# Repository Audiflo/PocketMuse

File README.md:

# PocketMage PDA
PocketMage is available on Crowd Supply! Check it out [here](https://pocketmage.org/back)!

@Ashtf 2025

## [Project Summary]

  This project is a PDA powered by an ESP32-S3 running a custom OS written in C++ using PlatformIO. This project utilizes an E-Ink and OLED screen in tandem to mitigate the refresh rate restrictions of an E-Ink panel while retaining the aesthetics and benefits of using E-Ink. This project is a work in progress and currently amounts to a simple GUI for navigating between apps, a text (.txt) file editor, and a basic file manager. More applications are planned for the future and a list of TO-DOs can be found below.

  At this point, the plan for this project is to get the software and hardware to maturity and once a finished product is achieved, a few things will happen. First, the project files (Code, KiCad schematics, 3D files) will be open-sourced and free for anyone to access. Next, I will likely begin selling kits that allow people to purchase all the parts required to build a device for themselves if they don't want to source the parts themselves. Finally, the community will be encouraged to help develop the software for the device and hopefully push it even further than I could myself.

  I will try my best to keep this GitHub up to date with the development of the device.

## [Getting Started]

Start with the docs site:

- [PocketMage Docs](https://tailsmandesign.github.io/PocketMage_PDA/docs/)
- [Build Environments](https://tailsmandesign.github.io/PocketMage_PDA/docs/development/build-environments)
- [Command Manual](https://tailsmandesign.github.io/PocketMage_PDA/docs/command-manual)
- [FAQ](https://tailsmandesign.github.io/PocketMage_PDA/docs/faq)
- [Scripting](https://tailsmandesign.github.io/PocketMage_PDA/docs/scripting)
- [App API Reference](https://tailsmandesign.github.io/PocketMage_PDA/docs/reference/app-api)

To build or extend apps, start with [APP_TEMPLATE.cpp](./Code/PocketMageOS/src/APP_TEMPLATE.cpp) and the [App API Reference](https://tailsmandesign.github.io/PocketMage_PDA/docs/reference/app-api).
The app walkthrough video is still useful for a first pass:
[Developing For the PocketMage](https://www.youtube.com/watch?v=3Ytc-3-BbMM)

## [Hardware]

- ESP32-S3 WROOM1 with 16 MB flash and 8 MB RAM. WiFi and Bluetooth supported.
- 3.1" 320x240px 1-bit SPI E-Ink panel (GDEQ031T10) with integrated driver
- 256x32px 1-bit SPI OLED (SSD1326, ER-OLED018-1W) with integrated driver
- MicroSD card slot with support for up to 2 TB
- TCA8418 I2C keyboard matrix IC
- Piezo buzzer (simple tones)
- Power button
- 1200 mAh pouch-style LiPo battery with JST PH (2 mm) connector
- USB Type-C connector
- PCF8563T I2C RTC module
- Expansion port with the following breakouts:
  - +3.3V
  - GND
  - I2C SDA
  - I2C SCL
  - SPI MOSI
  - SPI SCK
  - SPI MISO
  - GPIO A
  - GPIO B
  - GPIO C
  - GPIO D / UART TX (changeable with a solder jumper, default TX)
  - GPIO E / UART RX (changeable with a solder jumper, default RX)

## [Software]

- Text editor app (TXT)
- FileWiz file-management app
- Calendar app
- USB file transfer app
- COMM mesh chat app
- Settings app
- Tasks app
- Journal app
- Dictionary app (Lexicon)
- App loader for OTA apps
- Terminal app (Wrench scripting)
- SSH
- Commands supported through the home menu:
  - `roll dN` (dice roll, N = number of sides)
  - set time and date
  - directly open files in TXT or FileWiz by typing the name
  - and more

## [Planned Features]

- Timers and alarms
- E-book reader
- WiFi notes/calendar sync (Google Docs/Calendar)
- LoRa/Meshtastic add-on module
- Battery expansion add-on module
- Custom abbreviations
- Bluetooth keyboard support

## License

All files are distributed under the Apache-2.0 license:

PocketMage PDA - A clamshell note-taking and productivity device using E-Ink and OLED.

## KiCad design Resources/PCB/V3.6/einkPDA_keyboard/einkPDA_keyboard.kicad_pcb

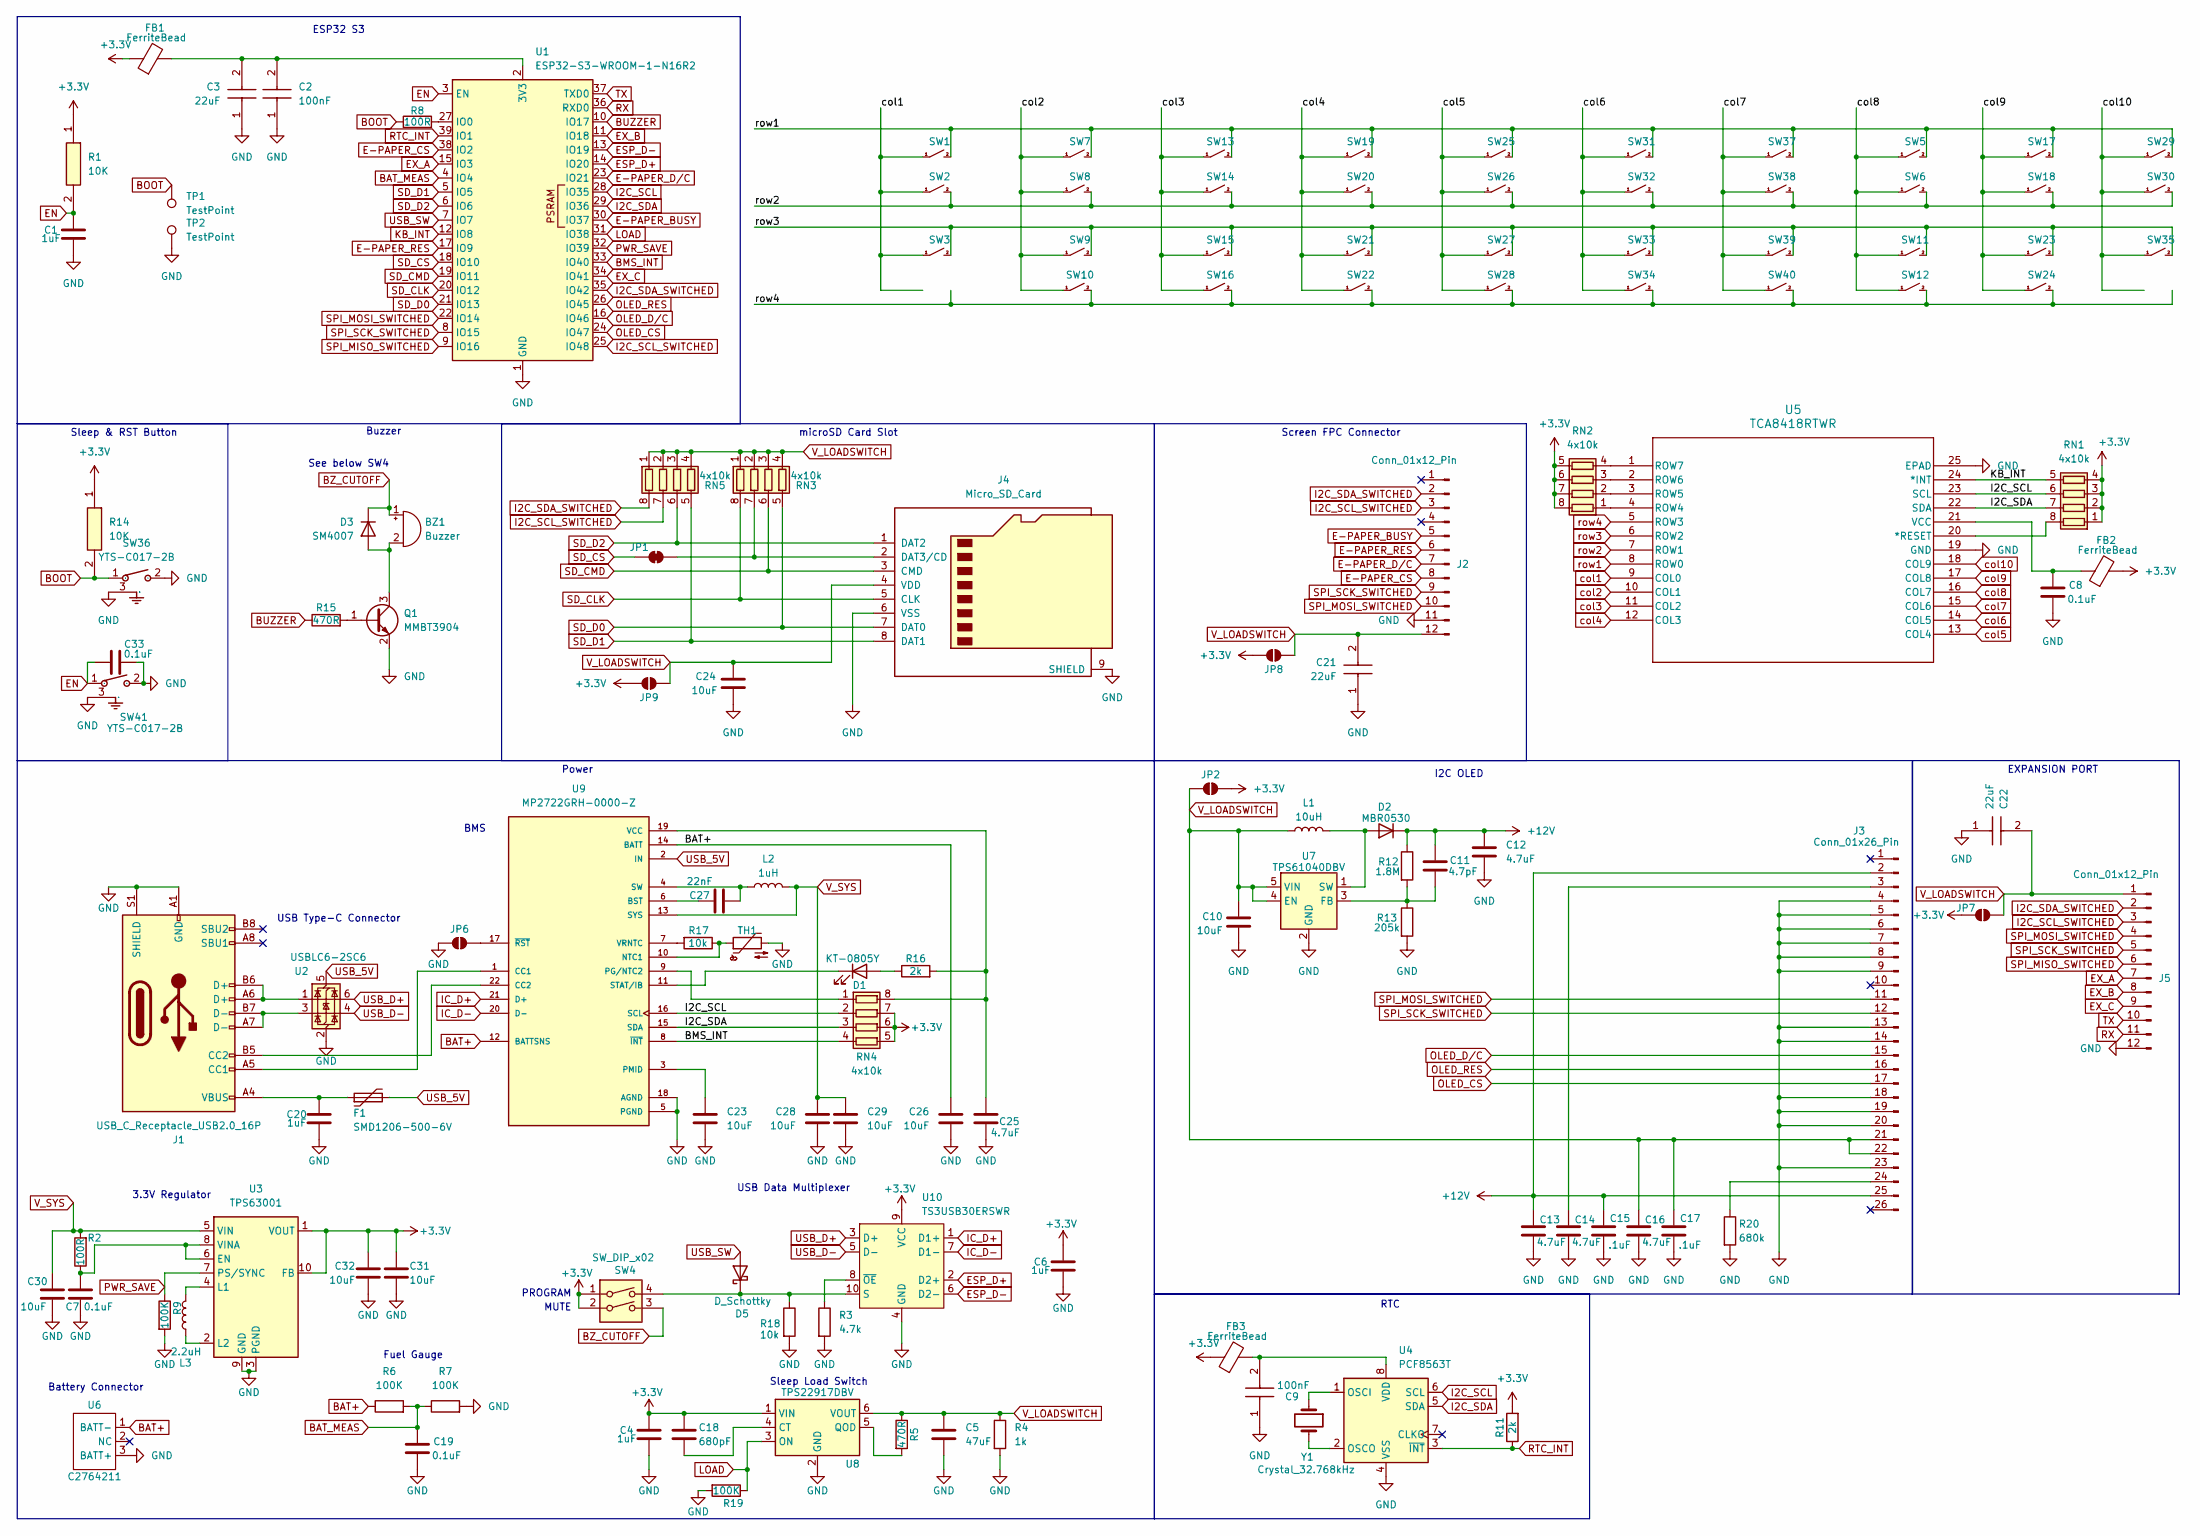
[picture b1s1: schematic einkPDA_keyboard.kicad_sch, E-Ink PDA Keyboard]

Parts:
BZ1: Buzzer; BUZ-SMD_3P_L5.0-W5.0-P3.50-TL; LCSC Part # C781883
C1, C4, C6, C20: 1uF; C_0603_1608Metric; LCSC Part # C15849
C2, C9: 100nF; C_0805_2012Metric; Mouser Part Number 603-CC805KRX7R9BB104
C3, C21, C22: 22uF; C_0805_2012Metric; Mouser Part Number 187-CL21A226MAQNNNE
C5: 47uF; C_0805_2012Metric; LCSC Part # C124129
C7, C8, C19, C33: 0.1uF; C_0402_1005Metric; LCSC Part # C1525
C10, C23, C26, C28, C29, C30, C31, C32: 10uF; C_0805_2012Metric; LCSC PART # C15850
C11: 4.7pF; C_0603_1608Metric; LCSC PART # C1669
C12, C13, C14, C16: 4.7uF; C_1206_3216Metric; LCSC PART # C29823
C15, C17: .1uF; C_0805_2012Metric; LCSC PART # C28233
C18: 680pF; C_0805_2012Metric; LCSC Part # C1754
C24: 10uF; C_0805_2012Metric; LCSC Part # C15850
C25: 4.7uF; C_0805_2012Metric; LCSC Part # C1779
C27: 22nF; C_0603_1608Metric; LCSC Part # C21122
D1: KT-0805Y; LED_0805_2012Metric; LCSC Part # C2296
D2: MBR0530; D_SOD-123; LCSC PART # C77336
D3: SM4007; D_SOD-123F; LCSC Part # C64898
D5: D_Schottky; D_SOD-323; LCSC Part # C191023
F1: SMD1206-500-6V; Fuse_1206_3216Metric; LCSC Part # C2760308
FB1, FB2, FB3: FerriteBead; L_0603_1608Metric; LCSC Part # C85831
J1: USB_C_Receptacle_USB2.0_16P; USB-TYPE-C-SMD_TYPE-C-16P-QTWT; LCSC Part # C5187472
J2, J5: Conn_01x12_Pin; AFC01-S12FCA-00; LCSC Part # C262661
J3: Conn_01x26_Pin; FPC-SMD_AFC24-S26FIA [DUAL-SIDE]; LCSC PART # C262684
J4: Micro_SD_Card; TF-SMD_503398-1892; LCSC Part # C428492
JP1: SolderJumper_2_Bridged; SolderJumper-2_P1.3mm_Bridged_RoundedPad1.0x1.5mm
JP2, JP6, JP7, JP8, JP9: SolderJumper_2_Open; SolderJumper-2_P1.3mm_Open_RoundedPad1.0x1.5mm
L1: 10uH; L_Chilisin_BMRx00060630; LCSC PART # C5189958
L2: 1uH; L_Ferrocore_DLG-0504; LCSC Part # C2929426
L3: 2.2uH; L_Wurth_WE-LQSH-3012; LCSC Part # C167747
Q1: MMBT3904; SOT-23; LCSC Part # C20526
R1, R14: 10K; R_0805_2012Metric; Mouser Part Number 303-0805W8F1002T5E
R2, R8: 100R; R_0603_1608Metric; LCSC Part # C22775
R3: 4.7k; R_0603_1608Metric; LCSC Part # C23162
R4: 1k; R_0603_1608Metric; LCSC Part # C21190
R5, R15: 470R; R_0805_2012Metric; LCSC Part # C17710
R6, R7, R9, R19: 100K; R_0603_1608Metric; LCSC Part # C25803
R11, R16: 2k; R_0805_2012Metric; LCSC Part # C17604
R12: 1.8M; R_0805_2012Metric; LCSC PART # C17399
R13: 205k; R_0805_2012Metric; LCSC PART # C218417
R17: 10k; R_0805_2012Metric; LCSC Part # C17414
R18: 10k; R_0603_1608Metric; LCSC Part # C25804
R20: 680k; R_0805_2012Metric; LCSC PART # C17797
RN1, RN2, RN3, RN4, RN5: 4x10k; R_Array_Concave_4x0603; LCSC Part # C29718
SW1, SW2, SW3, SW5, SW6, SW7, SW8, SW9, SW10, SW11, SW12, SW13, SW14, SW15, SW16, SW17, SW18, SW19, SW20, SW21, SW22, SW23, SW24, SW25, SW26, SW27, SW28, SW29, SW30, SW31, SW32, SW33, SW34, SW35, SW37, SW38, SW39, SW40: contact_pad_SINGLE
SW4: SW_DIP_x02; 2X_DIP_DHN-02-V-TR; LCSC Part # C224995
SW36, SW41: YTS-C017-2B; KEY-TH_3P-L4.5-W4.5-P3.0-EH; Manufacturer Part YTS-C017-2B; LCSC Part # C2910872
TH1: NTC; R_0603_1608Metric; LCSC Part # C76589
TP1, TP2: TestPoint; TestPoint_Pad_1.0x1.0mm
U1: ESP32-S3-WROOM-1-N16R2; ESP32-S3-WROOM-1; LCSC Part # C2913205
U2: USBLC6-2SC6; SOT-23-6; LCSC Part # C7519
U3: TPS63001; Texas_DRC0010J_ThermalVias; LCSC Part # C28060
U4: PCF8563T; SOIC-8_3.9x4.9mm_P1.27mm; LCSC Part # C7440
U5: TCA8418RTWR; RTW24_2P45X2P45; LCSC Part # C138713
U6: C2764211; CONN-SMD_532610271; LCSC Part # C2764211
U7: TPS61040DBV; SOT-23-5; LCSC PART # C7722
U8: TPS22917DBV; SOT-23-6; LCSC Part # C2680344
U9: MP2722GRH-0000-Z; IC_MP2722GRH-0000-Z; PARTREV 1.0; LCSC Part # C20099551
U10: TS3USB30ERSWR; UQFN-10_1.4x1.8mm_P0.4mm; LCSC Part # C73880
Y1: Crystal_32.768kHz; Crystal_SMD_3215-2Pin_3.2x1.5mm; LCSC Part # C5213671

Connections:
+3.3V: C4.2, C6.2, C18.1, C31.2, C32.2, FB1.1, FB2.2, FB3.1, JP2.2 (B), JP7.2 (B), JP8.2 (B), JP9.2 (B), R1.1, R11.2, R14.1, RN1.1 (R1.1), RN1.2 (R2.1), RN1.3 (R3.1), RN1.4 (R4.1), RN2.5 (R4.2), RN2.6 (R3.2), RN2.7 (R2.2), RN2.8 (R1.2), RN4.5 (R4.2), RN4.6 (R3.2), RN4.7 (R2.2), SW4.1, SW4.2, U3.1 (VOUT), U3.10 (FB), U8.1 (VIN), U10.9 (VCC)
+12V: C11.2, C12.1, C13.1, C15.1, D2.1 (K), J3.2, J3.25, R12.1
BAT+: C26.2, R6.1, U6.1 (BATT-), U9.12 (BATTSNS), U9.14 (BATT)
BAT_MEAS: C19.1, R6.2, R7.1, U1.4 (IO4)
BMS_INT: RN4.4 (R4.1), U1.33 (IO40), U9.8 (~INT)
BOOT: R8.1, R14.2, SW36.1, TP1.1
BUZZER: R15.1, U1.10 (IO17)
BZ_CUTOFF: BZ1.1 (+), D3.1 (K), SW4.3
E-PAPER_BUSY: J2.5, U1.30 (IO37)
E-PAPER_CS: J2.8, U1.38 (IO2)
E-PAPER_D/C: J2.7, U1.23 (IO21)
E-PAPER_RES: J2.6, U1.17 (IO9)
EN: C1.2, C33.1, R1.2, SW41.1, U1.3 (EN)
ESP_D+: U1.14 (IO20), U10.2 (D2+)
ESP_D-: U1.13 (IO19), U10.6 (D2-)
EX_A: J5.7, U1.15 (IO3)
EX_B: J5.8, U1.11 (IO18)
EX_C: J5.9, U1.34 (IO41)
GND: C1.1, C2.1, C3.1, C4.1, C5.2, C6.1, C7.2, C8.2, C9.1, C10.1, C12.2, C13.2, C14.2, C15.2, C16.2, C17.2, C19.2, C20.1, C21.1, C22.1, C23.1, C24.2, C25.2, C26.1, C28.1, C29.1, C30.1, C31.1, C32.1, C33.2, J1.A1 (GND), J1.A12 (GND), J1.B1 (GND), J1.B12 (GND), J1.S1 (SHIELD), J2.11, J3.4, J3.5, J3.6, J3.7, J3.8, J3.9, J3.13, J3.14, J3.18, J3.19, J3.20, J3.23, J4.6 (VSS), J4.9 (SHIELD), J5.12, JP6.1 (A), Q1.2 (E), R3.2, R4.2, R7.2, R9.2, R13.2, R18.2, R19.2, R20.2, SW36.2, SW36.3 (GND), SW41.2, SW41.3 (GND), TH1.2, TP2.1, U1.1 (GND), U1.40 (GND), U1.41 (GND), U2.2 (GND), U3.3 (PGND), U3.9 (GND), U3.11 (PGND), U4.4 (VSS), U5.19 (GND), U5.25 (EPAD), U6.3 (BATT+), U7.2 (GND), U8.2 (GND), U9.5 (PGND), U9.18 (AGND), U10.4 (GND)
I2C_SCL: RN1.6 (R3.2), RN4.2 (R2.1), U1.28 (IO35), U4.6 (SCL), U5.23 (SCL), U9.16 (SCL)
I2C_SCL_SWITCHED: J2.3, J5.3, RN5.7 (R2.2), U1.25 (IO48)
I2C_SDA: RN1.7 (R2.2), RN4.3 (R3.1), U1.29 (IO36), U4.5 (SDA), U5.22 (SDA), U9.15 (SDA)
I2C_SDA_SWITCHED: J2.2, J5.2, RN5.8 (R1.2), U1.35 (IO42)
IC_D+: U9.21 (D+), U10.1 (D1+)
IC_D-: U9.20 (D-), U10.7 (D1-)
KB_INT: RN1.5 (R4.2), U1.12 (IO8), U5.24 (*INT)
LOAD: R19.1, U1.31 (IO38), U8.3 (ON)
unnamed: BZ1.2 (-), D3.2 (A), Q1.3 (C)
unnamed: C20.2, F1.1, J1.A4 (VBUS), J1.A9 (VBUS), J1.B4 (VBUS), J1.B9 (VBUS)
unnamed: D1.2 (A), R16.1
unnamed: D1.1 (K), U9.11 (STAT/IB)
unnamed: D2.2 (A), L1.2, U7.1 (SW)
unnamed: D5.1 (K), R18.1, SW4.4, U10.10 (S)
unnamed: J1.A5 (CC1), U9.1 (CC1)
unnamed: J1.B5 (CC2), U9.22 (CC2)
unnamed: J1.A6 (D+), J1.B6 (D+), U2.1 (I/O1)
unnamed: J1.A7 (D-), J1.B7 (D-), U2.3 (I/O2)
unnamed: C14.1, J3.3
unnamed: J3.24, R20.1
unnamed: J4.2 (DAT3/CD), JP1.2 (B), RN3.7 (R2.2)
unnamed: JP6.2 (B), U9.17 (~RST)
unnamed: Q1.1 (B), R15.2
unnamed: RN1.8 (R1.2), U5.20 (*RESET)
unnamed: RN2.1 (R1.1), U5.4 (ROW4)
unnamed: RN2.2 (R2.1), U5.3 (ROW5)
unnamed: RN2.3 (R3.1), U5.2 (ROW6)
unnamed: RN2.4 (R4.1), U5.1 (ROW7)
unnamed: RN4.1 (R1.1), U9.9 (PG/NTC2)
unnamed: C25.1, R16.2, RN4.8 (R1.2), U9.19 (VCC)
unnamed: C2.2, C3.2, FB1.2, U1.2 (3V3)
unnamed: R8.2, U1.27 (IO0)
unnamed: C7.1, R2.1, U3.6 (EN), U3.8 (VINA)
unnamed: L3.1, U3.4 (L1)
unnamed: L3.2, U3.2 (L2)
unnamed: U4.1 (OSCI), Y1.1
unnamed: U4.2 (OSCO), Y1.2
unnamed: C9.2, FB3.2, U4.8 (VDD)
unnamed: C8.1, FB2.1, U5.21 (VCC)
unnamed: C11.1, R12.2, R13.1, U7.3 (FB)
unnamed: C18.2, U8.4 (CT)
unnamed: R5.2, U8.5 (QOD)
unnamed: C27.2, U9.6 (BST)
unnamed: R17.1, TH1.1, U9.10 (NTC1)
unnamed: C23.2, U9.3 (PMID)
unnamed: C27.1, L2.1, U9.4 (SW)
unnamed: R17.2, U9.7 (VRNTC)
unnamed: R3.1, U10.8 (~OE)
OLED_CS: J3.17, U1.24 (IO47)
OLED_D/C: J3.15, U1.16 (IO46)
OLED_RES: J3.16, U1.26 (IO45)
PWR_SAVE: R9.1, U1.32 (IO39), U3.7 (PS/SYNC)
RTC_INT: R11.1, U1.39 (IO1), U4.3 (~INT)
RX: J5.11, U1.36 (RXD0)
SD_CLK: J4.5 (CLK), RN3.8 (R1.2), U1.20 (IO12)
SD_CMD: J4.3 (CMD), RN3.6 (R3.2), U1.19 (IO11)
SD_CS: JP1.1 (A), U1.18 (IO10)
SD_D0: J4.7 (DAT0), RN3.5 (R4.2), U1.21 (IO13)
SD_D1: J4.8 (DAT1), RN5.5 (R4.2), U1.5 (IO5)
SD_D2: J4.1 (DAT2), RN5.6 (R3.2), U1.6 (IO6)
SPI_MISO_SWITCHED: J5.6, U1.9 (IO16)
SPI_MOSI_SWITCHED: J2.10, J3.11, J5.4, U1.22 (IO14)
SPI_SCK_SWITCHED: J2.9, J3.12, J5.5, U1.8 (IO15)
TX: J5.10, U1.37 (TXD0)
USB_5V: F1.2, U2.5 (VBUS), U9.2 (IN)
USB_D+: U2.6 (I/O1), U10.3 (D+)
USB_D-: U2.4 (I/O2), U10.5 (D-)
USB_SW: D5.2 (A), U1.7 (IO7)
V_LOADSWITCH: C5.1, C10.2, C16.1, C17.1, C21.2, C22.2, C24.1, J2.12, J3.21, J3.22, J4.4 (VDD), J5.1, JP2.1 (A), JP7.1 (A), JP8.1 (A), JP9.1 (A), L1.1, R4.1, R5.1, RN3.1 (R1.1), RN3.2 (R2.1), RN3.3 (R3.1), RN3.4 (R4.1), RN5.1 (R1.1), RN5.2 (R2.1), RN5.3 (R3.1), RN5.4 (R4.1), U7.4 (EN), U7.5 (VIN), U8.6 (VOUT)
V_SYS: C28.2, C29.2, C30.2, L2.2, R2.2, U3.5 (VIN), U9.13 (SYS)
col1: SW1.1, SW2.1, SW3.1, U5.9 (COL0)
col2: SW7.1, SW8.1, SW9.1, SW10.1, U5.10 (COL1)
col3: SW13.1, SW14.1, SW15.1, SW16.1, U5.11 (COL2)
col4: SW19.1, SW20.1, SW21.1, SW22.1, U5.12 (COL3)
col5: SW25.1, SW26.1, SW27.1, SW28.1, U5.13 (COL4)
col6: SW31.1, SW32.1, SW33.1, SW34.1, U5.14 (COL5)
col7: SW37.1, SW38.1, SW39.1, SW40.1, U5.15 (COL6)
col8: SW5.1, SW6.1, SW11.1, SW12.1, U5.16 (COL7)
col9: SW17.1, SW18.1, SW23.1, SW24.1, U5.17 (COL8)
col10: SW29.1, SW30.1, SW35.1, U5.18 (COL9)
row1: SW1.2, SW5.2, SW7.2, SW13.2, SW17.2, SW19.2, SW25.2, SW29.2, SW31.2, SW37.2, U5.8 (ROW0)
row2: SW2.2, SW6.2, SW8.2, SW14.2, SW18.2, SW20.2, SW26.2, SW30.2, SW32.2, SW38.2, U5.7 (ROW1)
row3: SW3.2, SW9.2, SW11.2, SW15.2, SW21.2, SW23.2, SW27.2, SW33.2, SW35.2, SW39.2, U5.6 (ROW2)
row4: SW10.2, SW12.2, SW16.2, SW22.2, SW24.2, SW28.2, SW34.2, SW40.2, U5.5 (ROW3)

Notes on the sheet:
ESP32 S3
RTC
Screen FPC Connector
PROGRAM
Buzzer
Battery Connector
See below SW4
Power
microSD Card Slot
Fuel Gauge
Sleep Load Switch
USB Data Multiplexer
USB Type-C Connector
3.3V Regulator
EXPANSION PORT
Sleep & RST Button
MUTE
BMS
I2C OLED

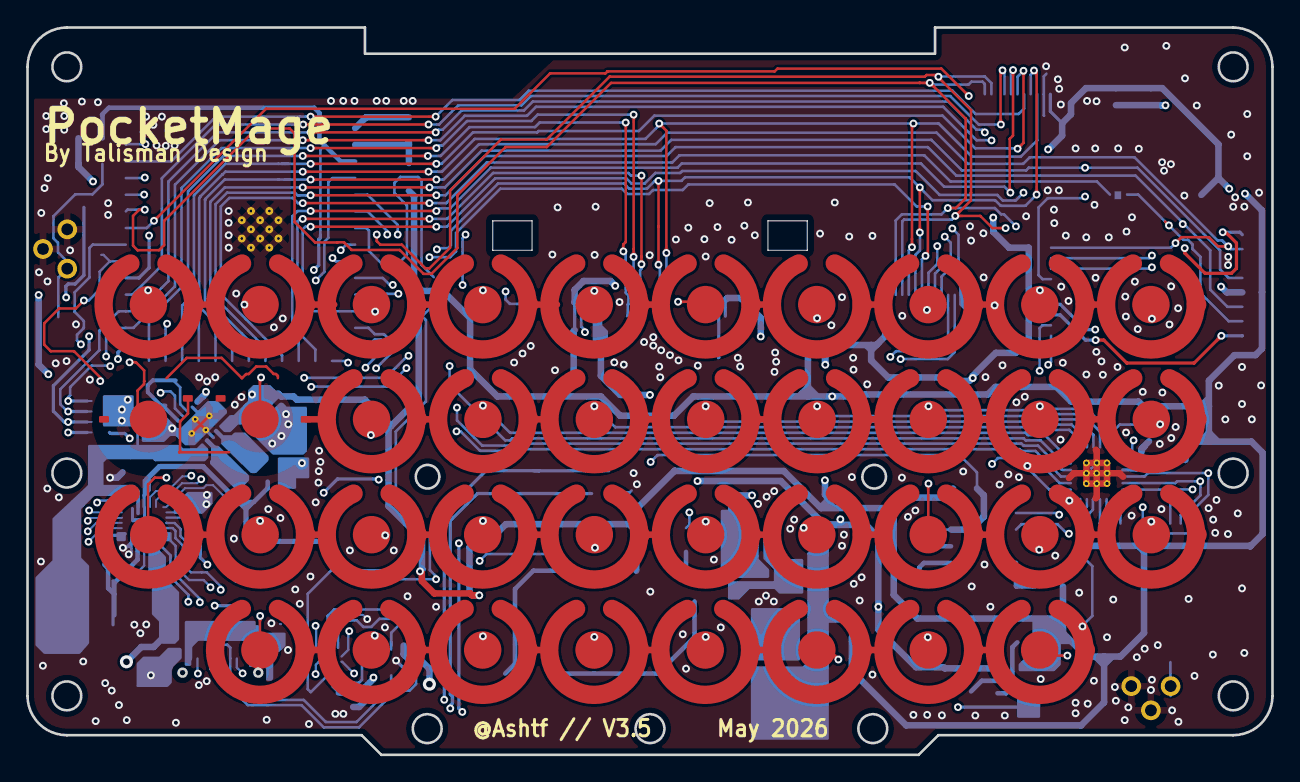
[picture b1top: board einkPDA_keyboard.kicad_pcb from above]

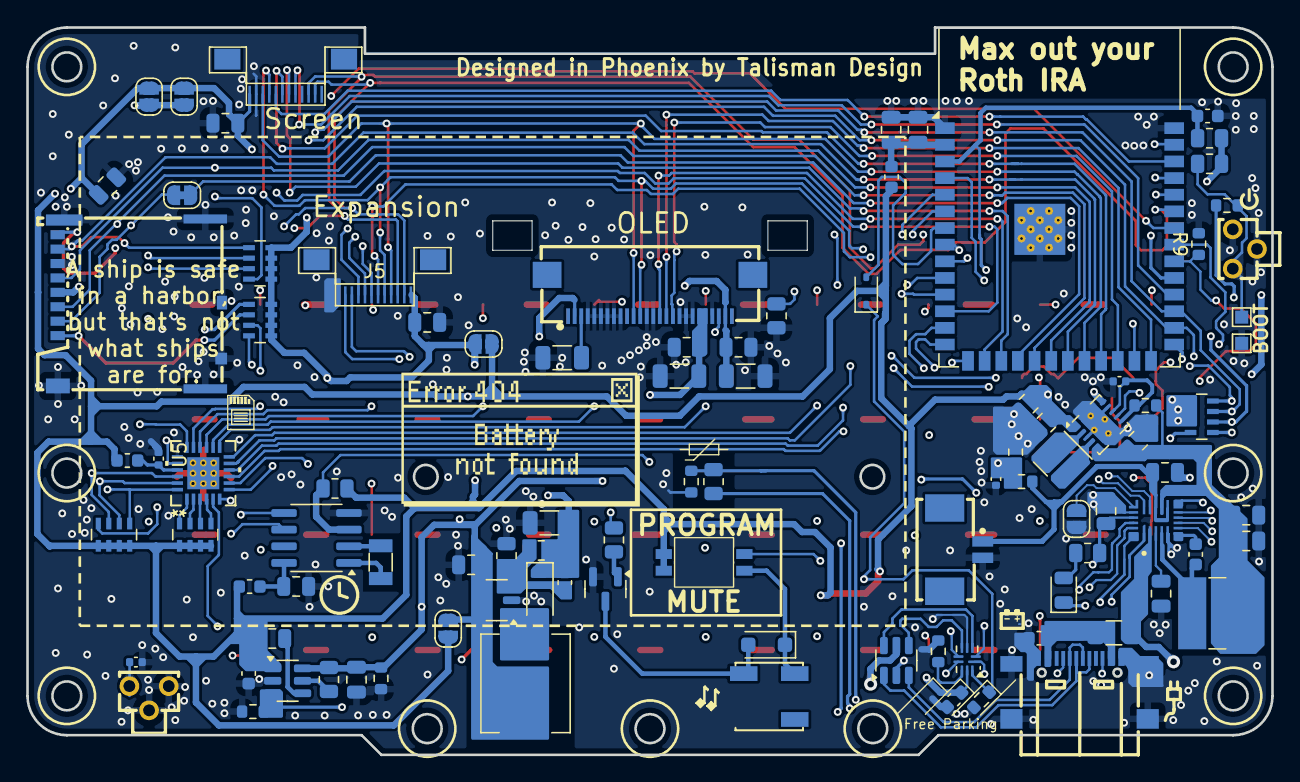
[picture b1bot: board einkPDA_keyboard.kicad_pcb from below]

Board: 4 copper layers, 95.0 x 55.5 mm, 136 parts (98 on the bottom side), 103 nets.

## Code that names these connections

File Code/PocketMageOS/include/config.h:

#ifndef CONFIG_H
#define CONFIG_H

// OTA App
// Is this an OTA APP? // OTA_APP: set -DOTA_APP_FLAG=1 in platformio.ini
#if OTA_APP_FLAG
#define OTA_APP true
#else
#define OTA_APP false
#endif

// CONFIGURATION & SETTINGS
////////////////////////////////////////////////////////////////////////////////////////////////////////////////////////////|
#define KB_COOLDOWN 3                           // Keypress cooldown
#define MAX_FILES 10                            // Number of files to store
#define FORMAT_SPIFFS_IF_FAILED true            // Format the SPIFFS filesystem if mount fails
#define SLEEPMODE "TEXT"                        // TEXT, SPLASH, CLOCK
#define TXT_APP_STYLE 1                         // 0: Old Style (NOT SUPPORTED), 1: New Style
#define SET_CLOCK_ON_UPLOAD false               // Should system clock be set automatically on code upload?
#define TOUCH_TIMEOUT_MS 1200                   // Delay after scrolling to return to typing mode (ms)
#define SYS_METADATA_FILE "/sys/SDMMC_META.txt" // File path to the file system metadata file
#define POWER_SAVE_FREQ 40                      // CPU freq for power save mode
#define IDLE_TIME 20000                         // time to wait for mage idle (ms)

// Full refresh after N refreshes (CHANGE WITH CAUTION)
#define FAST_REFRESH_AFTER 5   // Fast/partial mode: datasheet clean-every-5
#if POCKETMAGE_HW_VERSION == 2
  #define FULL_REFRESH_AFTER 10 // Prod legacy uses N=10                    
#else
  #define FULL_REFRESH_AFTER 5  // Beta needs N=5
#endif
////////////////////////////////////////////////////////////////////////////////////////////////////////////////////////////|

// PIN DEFINITION
#define I2C_SCL       35
#define I2C_SDA       36
#define SWITCHED_I2C_SDA  42
#define SWITCHED_I2C_SCL  48
#define MPR121_ADDR   0x5A
#define MP2722_ADDR   0x3F
#define USB_MUX_PIN   7

#define KB_IRQ        8
#define PWR_BTN       0 
#define BAT_SENS      4
#define CHRG_SENS     39
#define RTC_INT       1 
#define LOAD_SWITCH   38

// SPI
#define SPI_MOSI      14
#define SPI_SCK       15

// OLED
#define OLED_CS       47
#define OLED_DC       46
#define OLED_RST      45

// E Ink
#define EPD_CS        2
#define EPD_DC        21
#define EPD_RST       9
#define EPD_BUSY      37

// SDMMC mode
#define SD_CLK        12
#define SD_CMD        11
#define SD_D0         13
#define SD_D1         5
#define SD_D2         6
#define SD_D3         10

// SDSPI mode
#define SD_CS         10
#define SD_MOSI       11
#define SD_SCK        12
#define SD_MISO       13

#define BZ_PIN        17

// ===================== SYSTEM SETTINGS =====================
// Persistent preferences
extern int TIMEOUT;              // Auto sleep timeout (seconds)
extern bool DEBUG_VERBOSE;       // Extra debug output
extern bool SYSTEM_CLOCK;        // Show clock on screen
extern bool SHOW_YEAR;           // Show year in clock
extern bool SAVE_POWER;          // Enable power saving mode
extern bool ALLOW_NO_MICROSD;    // Allow running without SD card
extern bool HOME_ON_BOOT;        // Start home app on boot
extern bool FAST_REFRESH;        // Enable experimental fast partial refresh mode
extern int OLED_BRIGHTNESS;      // OLED brightness (0-255)
extern int OLED_MAX_FPS;         // OLED max FPS
extern bool MUTE_BUZZER;         // Mute the buzzer
extern bool SD_SPI_COMPATIBILITY;

#endif

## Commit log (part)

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2026-03-29 Fix mage idle not working
2026-03-29 Add progress line to TXT
2026-03-29 Fix macos apploader issue
2026-03-30 Skip MacOS metadata files in wiz
2026-04-09 Update fmt.Println message from 'Hello' to 'Goodbye'
2026-04-13 Prevent overwriting current build during backup
    Added a check to skip preserving the current build when backing up releases.
2026-04-13 Improve error message for manifest loading
    Updated error message display for manifest load errors.
2026-04-21 WIP chat app
2026-04-23 Reorganize and Docs
2026-04-23 Dark mode!!!
2026-04-25 Rename index.md to readme.md
2026-04-26 Fix directory change command in publish-docs.yml
2026-04-26 Rename readme.md to index.md
2026-04-26 Enhance comments for OTA_APP in APP_TEMPLATE.cpp
    Updated comments to clarify OTA_APP functionality and usage.
2026-04-27 Add Wrench API Reference documentation
    This document provides a comprehensive reference for the Wrench script bindings available in PocketMage OS, detailing functions for input/output, display updates, hardware interactions, filesystem op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
2026-05-01 Production boards implementation
2026-05-02 Update Screen PCB Silkscreens
2026-05-03 add mkdir to "help" list
2026-05-03 command to set large or small font in terminal
2026-05-03 Rename API Reference to Scripting Reference
2026-05-16 Fix formatting
2026-05-25 Meshtastic Add-On PCB WIP
2026-06-01 Remove FN legends from keyboard silkscreen
2026-06-15 Plot twist, it works now
2026-06-16 Tasks app scrolling and long task name truncation
2026-06-16 Basic emoticons introduced by holding TAB and pressing "."
2026-06-17 Fix #260 and add U8g2 fork
2026-06-19 Symlinks
2026-06-19 Kinda wip core
2026-06-19 Whaddya know, it crashes :/
2026-06-19 It loads but doesn't play, oh joy
2026-06-19 Improvements, still no playing
2026-06-19 I can hear only static
2026-06-19 Yeah i thought this would work NOPE
2026-06-20 I mean it kinda works but it's not 2x speed or maybe it is
    but it's like parts of the mp3 is skipped
2026-06-20 THE ENTIRE AUDIO IS THERE
2026-06-20 Full song plays now but it's fast but this is so fragileee
2026-06-20 I give up on manual
2026-06-20 AAAA STATIC ARE YOU KIDDING MEEEEE
2026-06-20 I can hear it... but it's kinda quiet and slow
2026-06-21 Hey it's a bit louder
    BUT PITCH WHY
2026-06-21 YAY IT WORKS
2026-06-21 Bug fixes
2026-06-21 Album art but PNG OMG and a jpeg bugfix
2026-06-21 CI™️
2026-06-21 chore: auto-build PocketMuse.tar
2026-06-21 OH SHOOT README
2026-06-21 Revert "Replace Font Headers with U8g2"
